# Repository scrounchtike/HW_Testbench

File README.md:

# Template_Hardware
see [KiCad_Library](https://github.com/EclipseETS/KiCad_Library) for detailed instructions

# Structure de projet
| [Nom de votre projet] |                    |        |
|:---:                  | :---:              | :---:  |
|↳                      | Calculs            |        |
|↳                      | DOC                |        |
|↳                      | [Nom du prototype] |        |
|                       |↳                   | [Version du PCB] |

# Utilisation  
1. Demander à un admin de créer un nouveau repo à partir du repo [Template_Hardware](https://github.com/EclipseETS/Template_Hardware).
2. Cloner le nouveau repo sur votre ordinateur.
3. Remplacer les noms des fichiers dans **Project_Template** avec le nom de votre projet **SAUF Project_Template.kicad_wks** .
4. Renommer le dossier **Project_Template** avec la version (Ex.V1,V2 ...) **La hiérarchie de projet doit ressembler à E10/V1/**.
5. Commit et Push les changements au projet. **Les projets HW travaillent directement dans la branche master**

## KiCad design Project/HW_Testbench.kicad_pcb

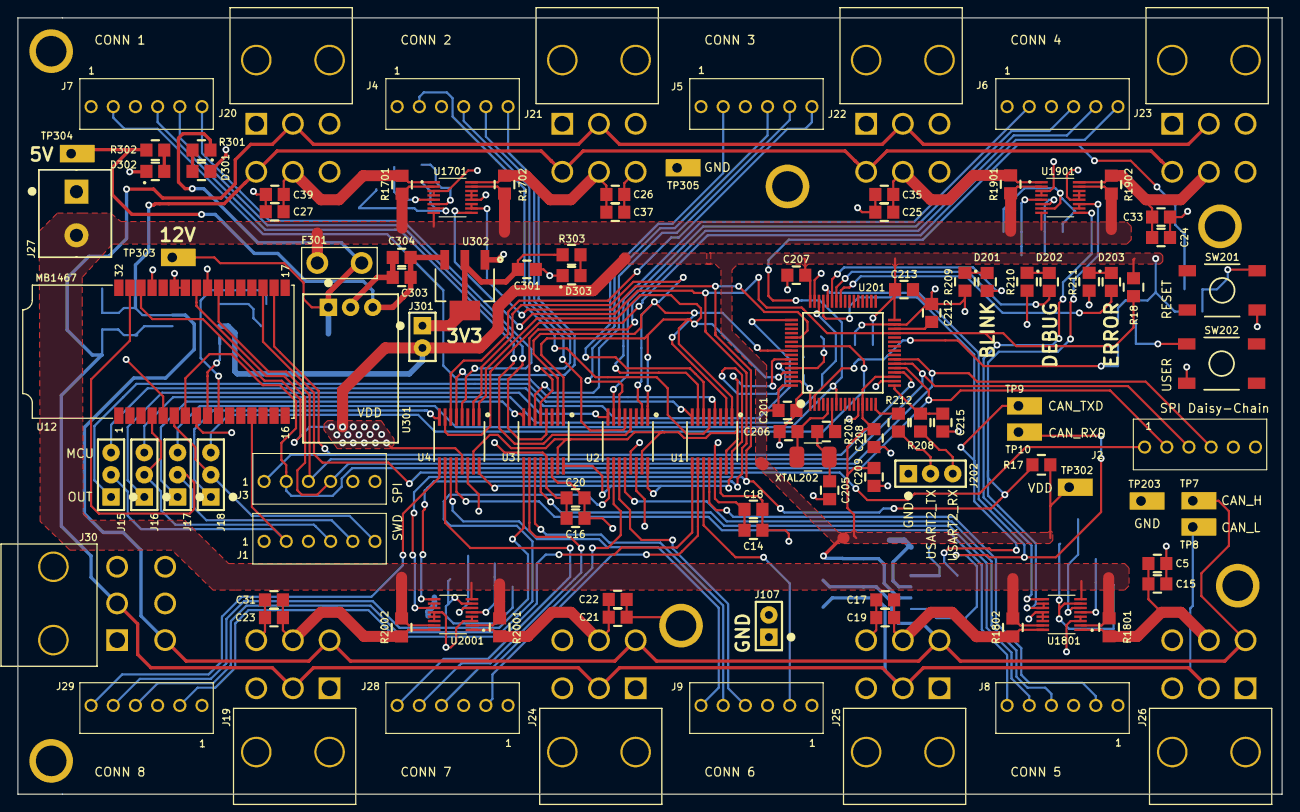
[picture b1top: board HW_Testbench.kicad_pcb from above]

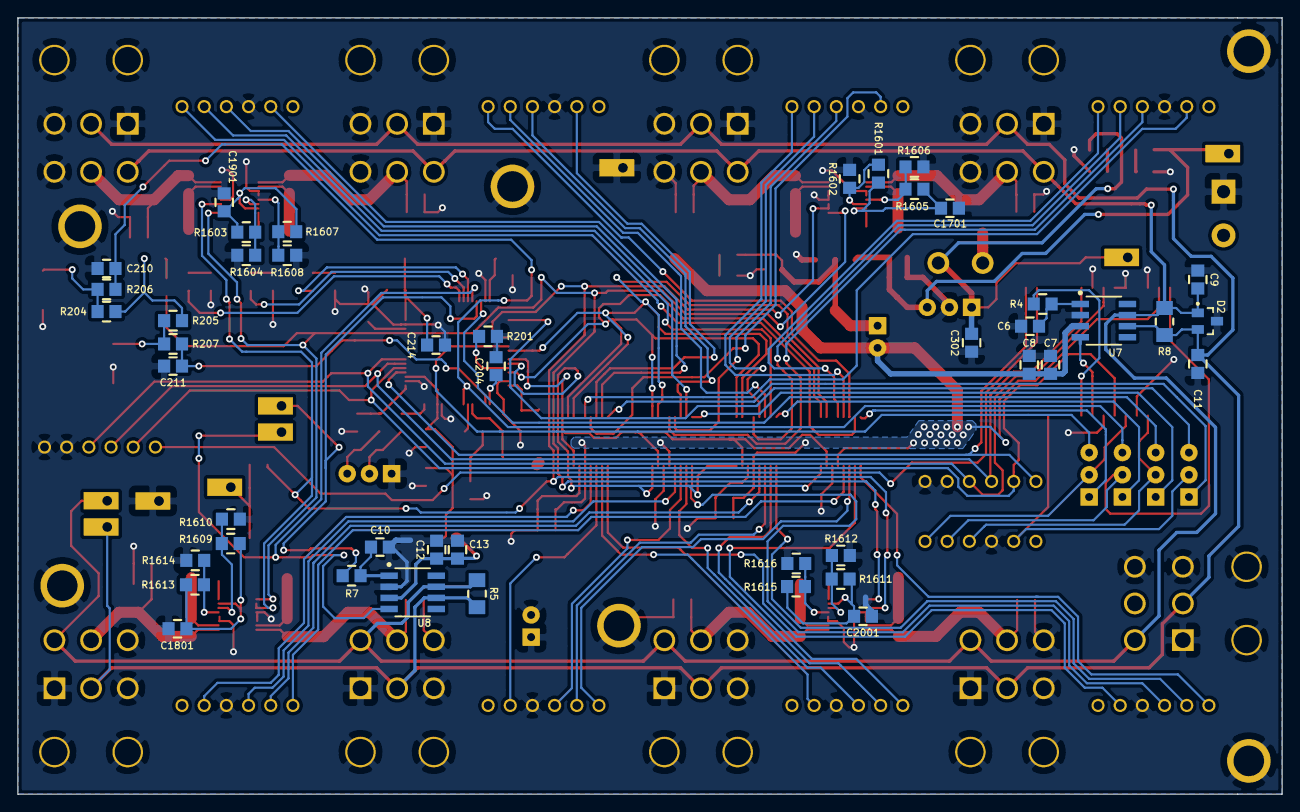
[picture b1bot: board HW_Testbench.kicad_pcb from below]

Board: 2 copper layers, 144.8 x 88.9 mm, 161 parts (45 on the bottom side), 111 nets.

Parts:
C5, C7, C12, C17, C18, C20, C21, C31, C33, C35, C37, C39, C204, C208: 885012107015; C0805
C6, C9, C10, C11: 885012207080; C0805
C8, C13, C14, C15, C16, C19, C22, C23, C24, C25, C26, C27, C201, C207, C210, C211, C213, C214, C1701, C1801, C1901, C2001: 885012207098; C0805
C205, C206, C215: 885012007053; C0805
C209: 885012207092; C0805
C212, C302, C303: 885012107018; C0805
C301: 885012107005; C0805
C304: 885012107014; C0805
D2: D1213A-02SOL-7; SOT-23-3
D201, D301, D302, D303: 150080VS75000; LED_0805_GREEN
D202: 150080YS75000; LED_0805_YELLOW
D203: 150080RS75000; LED_0805_RED
F301: 39511000440; TE5_395
H1, H2, H3, H4, H6, H7: Mounting-Hole-M3; Mounting_Hole_3mm
J1, J2, J3, J4, J5, J6, J7, J8, J9, J28, J29: 61900611121
J15, J16, J17, J18, J202: Header_Male_Pin_2.54mm_1X3_,_Unshrouded; Headers_2.54mm_1X3
J19, J20, J21, J22, J23, J24, J25, J26, J30: 649006227222
J27: 1935161
J107, J301: Header_Male_Pin_2.54mm_1X2_,_Unshrouded; Headers_2.54mm_1X2
R4, R7, R206, R207: RC0805JR-07100RL; R0805
R5, R8: RC1206JR-07120RL; R1206
R17, R18, R204, R205, R208, R301: RC0805JR-074K7L; R0805
R201: RC0805JR-0710KL; R0805
R203, R1601, R1602, R1603, R1604, R1605, R1606, R1607, R1608, R1609, R1610, R1611, R1612, R1613, R1614, R1615, R1616: RC0805JR-070RL; R0805
R209, R210, R211, R303: RC0805JR-07470RL; R0805
R212, R302: RC0805JR-071KL; R0805
R1701, R1702, R1801, R1802, R1901, R1902, R2001, R2002: ERJ-6LWFR005V; R0805
SW201, SW202: PTS645SM43SMTR92; PTS645_6X6X4_SMD
TP7, TP8, TP9, TP10, TP203, TP302, TP303, TP304, TP305: Test_Point_THM; Keystone_5001
U1, U2, U3, U4: TMUX1208PWR; TSSOP-16
U7, U8: SN65HVD232DR; SOIC-8
U12: STLINK-V3MODS; MOD_STLINK-V3M_MB1467
U201: STM32F446RE; LQFP-64
U301: OKI-78SR-5_1.5-W36H-C; OKI-78SR_Horizontal
U302: AZ1117IH-3.3TRG1; SOT-223-3
U1701, U1801, U1901, U2001: LTC2992IMS_PBF; AnalogDevices_16-MSOP
XTAL202: 7A-8.000MAHJ-T; TXC_7A_Series

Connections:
3.3V: C301.2, J301.1, R303.2, U302.2, U302.4
5V: C303.2, C304.2, R302.2, TP304.1, U301.3, U302.3
12V: C302.2, F301.2, R301.2, TP303.1, U301.1
/ADR_0: U1.1, U2.1, U3.1, U4.1, U201.61
/ADR_1: U1.16, U2.16, U3.16, U4.16, U201.59
/ADR_2: U1.15, U2.15, U3.15, U4.15, U201.58
/CAN1_RXD: TP10.1, U8.4, U201.44
/CAN1_TXD: R7.1, TP9.1, U201.45
/CAN_Connectors/12V_Conn1: C27.1, C39.2, J20.5, R1701.1, U1701.1
/CAN_Connectors/12V_Conn2: C26.1, C37.2, J21.5, R1702.2, U1701.16
/CAN_Connectors/12V_Conn3: C25.1, C35.2, J22.5, R1901.1, U1901.1
/CAN_Connectors/12V_Conn4: C24.1, C33.2, J23.5, R1902.2, U1901.16
/CAN_Connectors/12V_Conn5: C5.2, C15.1, J26.5, R1801.1, U1801.1
/CAN_Connectors/12V_Conn6: C17.2, C19.1, J25.5, R1802.2, U1801.16
/CAN_Connectors/12V_Conn7: C21.2, C22.1, J24.5, R2001.1, U2001.1
/CAN_Connectors/12V_Conn8: C23.1, C31.2, J19.5, R2002.2, U2001.16
/CAN_Connectors/CAN_H: C9.1, D2.1, J19.4, J20.4, J21.4, J22.4, J23.4, J24.4, J25.4, J26.4, J30.4, R5.1, R8.1, TP7.1, U7.7, U8.7
/CAN_Connectors/CAN_L: C11.1, D2.2, J19.2, J20.2, J21.2, J22.2, J23.2, J24.2, J25.2, J26.2, J30.2, R5.2, R8.2, TP8.1, U7.6, U8.6
/CAN_Connectors/CurrentSense/sheet60485D35/I2C_ADR0: R1601.2, R1602.1, U1701.6
/CAN_Connectors/CurrentSense/sheet60485D35/I2C_ADR1: R1605.2, R1606.1, U1701.5
/CAN_Connectors/CurrentSense/sheet60485D35/INTVcc: C1701.1, R1601.1, R1605.1, U1701.7
/CAN_Connectors/CurrentSense/sheet60485D36/I2C_ADR0: R1609.2, R1610.1, U1801.6
/CAN_Connectors/CurrentSense/sheet60485D36/I2C_ADR1: R1613.2, R1614.1, U1801.5
/CAN_Connectors/CurrentSense/sheet60485D36/INTVcc: C1801.1, R1609.1, R1613.1, U1801.7
/CAN_Connectors/CurrentSense/sheet60485D37/I2C_ADR0: R1603.2, R1604.1, U1901.6
/CAN_Connectors/CurrentSense/sheet60485D37/I2C_ADR1: R1607.2, R1608.1, U1901.5
/CAN_Connectors/CurrentSense/sheet60485D37/INTVcc: C1901.1, R1603.1, R1607.1, U1901.7
/CAN_Connectors/CurrentSense/sheet60485D38/I2C_ADR0: R1611.2, R1612.1, U2001.6
/CAN_Connectors/CurrentSense/sheet60485D38/I2C_ADR1: R1615.2, R1616.1, U2001.5
/CAN_Connectors/CurrentSense/sheet60485D38/INTVcc: C2001.1, R1611.1, R1615.1, U2001.7
/CONN_NRST: J1.5, J17.2, U12.31
/CONN_SWCLK: J1.2, J15.2, U12.13
/CONN_SWDIO: J1.4, J16.2, U12.4
/CONN_SWO: J1.6, J18.2, U12.6
/CS_SCL: R18.2, U201.29, U1701.9, U1801.9, U1901.9, U2001.9
/CS_SDA: R17.2, U201.53, U1701.10, U1701.11, U1801.10, U1801.11, U1901.10, U1901.11, U2001.10, U2001.11
/DAISYCHAIN_SPI_NSS: J2.1, U12.19
/MCU_NRST: C210.1, J17.3, R206.2, U201.7
/MCU_SWCLK: J15.3, U201.49
/MCU_SWDIO: J16.3, U201.46
/MCU_SWO: J18.3, U201.55
/OUT_NRST: J17.1, U3.8
/OUT_SWCLK: J15.1, U1.8
/OUT_SWDIO: J16.1, U2.8
/OUT_SWO: J18.1, U4.8
/PA4: J3.1, U12.18, U201.20
/PA5: J2.2, J3.2, U12.7, U201.21
/PA6: J2.3, J3.3, U12.23, U201.22
/PA7: J2.4, J3.4, U12.25, U201.23
/PB4: U1.2, U2.2, U3.2, U4.2, U201.56
/STLINK_CAN_RXD: U7.4, U12.9
/STLINK_CAN_TXD: R4.1, U12.10
/STM32F446/BLINK: D201.2, U201.43
/STM32F446/DEBUG: D202.2, U201.42
/STM32F446/ERROR: D203.2, U201.41
/STM32F446/HSE_IN: C206.1, U201.5, XTAL202.2
/STM32F446/HSE_OUT: R203.1, U201.6
/STM32F446/PA2: R212.2, U201.16
/STM32F446/PA3: C215.2, R208.2, U201.17
/STM32F446/USART2_RX: J202.3, R208.1
/STM32F446/USART2_TX: J202.2, R212.1
/STM32F446/USER_BTN: C211.1, R207.2, U201.2
/SWD_Connecteurs/NRST_1: J7.5, U3.4
/SWD_Connecteurs/NRST_2: J4.5, U3.5
/SWD_Connecteurs/NRST_3: J5.5, U3.6
/SWD_Connecteurs/NRST_4: J6.5, U3.7
/SWD_Connecteurs/NRST_5: J8.5, U3.12
/SWD_Connecteurs/NRST_6: J9.5, U3.11
/SWD_Connecteurs/NRST_7: J28.5, U3.10
/SWD_Connecteurs/NRST_8: J29.5, U3.9
/SWD_Connecteurs/SWCLK_1: J7.2, U1.4
/SWD_Connecteurs/SWCLK_2: J4.2, U1.5
/SWD_Connecteurs/SWCLK_3: J5.2, U1.6
/SWD_Connecteurs/SWCLK_4: J6.2, U1.7
/SWD_Connecteurs/SWCLK_5: J8.2, U1.12
/SWD_Connecteurs/SWCLK_6: J9.2, U1.11
/SWD_Connecteurs/SWCLK_7: J28.2, U1.10
/SWD_Connecteurs/SWCLK_8: J29.2, U1.9
/SWD_Connecteurs/SWDIO_1: J7.4, U2.4
/SWD_Connecteurs/SWDIO_2: J4.4, U2.5
/SWD_Connecteurs/SWDIO_3: J5.4, U2.6
/SWD_Connecteurs/SWDIO_4: J6.4, U2.7
/SWD_Connecteurs/SWDIO_5: J8.4, U2.12
/SWD_Connecteurs/SWDIO_6: J9.4, U2.11
/SWD_Connecteurs/SWDIO_7: J28.4, U2.10
/SWD_Connecteurs/SWDIO_8: J29.4, U2.9
/SWD_Connecteurs/SWO_1: J7.6, U4.4
/SWD_Connecteurs/SWO_2: J4.6, U4.5
/SWD_Connecteurs/SWO_3: J5.6, U4.6
/SWD_Connecteurs/SWO_4: J6.6, U4.7
/SWD_Connecteurs/SWO_5: J8.6, U4.12
/SWD_Connecteurs/SWO_6: J9.6, U4.11
/SWD_Connecteurs/SWO_7: J28.6, U4.10
/SWD_Connecteurs/SWO_8: J29.6, U4.9
/VBat: C204.2, U201.1
CAN_PWR: F301.1, J27.2, R1701.2, R1702.1, R1801.2, R1802.1, R1901.2, R1902.1, R2001.2, R2002.1, U1701.2, U1701.8, U1701.15, U1801.2, U1801.8, U1801.15, U1901.2, U1901.8, U1901.15, U2001.2, U2001.8, U2001.15
DGND: C5.1, C6.2, C7.1, C8.1, C9.2, C10.2, C11.2, C12.1, C13.1, C14.1, C15.2, C16.1, C17.1, C18.2, C19.2, C20.2, C21.1, C22.2, C23.2, C24.2, C25.2, C26.2, C27.2, C31.1, C33.1, C35.1, C37.1, C39.1, C201.1, C204.1, C205.1, C206.2, C207.2, C208.1, C209.1, C210.2, C211.2, C212.1, C213.2, C214.2, C215.1, C301.1, C302.1, C303.1, C304.1, C1701.2, C1801.2, C1901.2, C2001.2, D2.3, D301.1, D302.1, D303.1, H1.1, H2.1, H3.1, H4.1, H6.1, H7.1, J1.3, J2.5, J2.6, J3.5, J3.6, J4.3, J5.3, J6.3, J7.3, J8.3, J9.3, J19.1, J19.3, J19.6, J19.7, J19.8, J20.1, J20.3, J20.6, J20.7, J20.8, J21.1, J21.3, J21.6, J21.7, J21.8, J22.1, J22.3, J22.6, J22.7, J22.8, J23.1, J23.3, J23.6, J23.7, J23.8, J24.1, J24.3, J24.6, J24.7, J24.8, J25.1, J25.3, J25.6, J25.7, J25.8, J26.1, J26.3, J26.6, J26.7, J26.8, J27.1, J28.3, J29.3, J30.1, J30.3, J30.6, J30.7, J30.8, J107.1, J107.2, J202.1, R201.1, R209.1, R210.1, R211.1, R1602.2, R1604.2, R1606.2, R1608.2, R1610.2, R1612.2, R1614.2, R1616.2, SW201.4, SW202.3, TP203.1, TP305.1, U1.14, U2.14, U3.14, U4.14, U7.2, U8.2, U12.5, U12.8, U12.24, U12.26, U12.27, U12.29, U201.12, U201.18, U201.31, U201.47, U201.63, U301.2, U302.1, U1701.3, U1701.4, U1701.12, U1701.13, U1701.14, U1801.3, U1801.4, U1801.12, U1801.13, U1801.14, U1901.3, U1901.4, U1901.12, U1901.13, U1901.14, U2001.3, U2001.4, U2001.12, U2001.13, U2001.14
unnamed: C6.1, R4.2, U7.1
unnamed: C10.1, R7.2, U8.1
unnamed: C205.2, R203.2, XTAL202.1
unnamed: C212.2, U201.30
unnamed: D201.1, R209.2
unnamed: D202.1, R210.2
unnamed: D203.1, R211.2
unnamed: D301.2, R301.1
unnamed: D302.2, R302.1
unnamed: D303.2, R303.1
unnamed: R201.2, U201.60
unnamed: R204.1, R206.1, SW201.2
unnamed: R205.1, R207.1, SW202.1
VDD: C7.2, C8.2, C12.2, C13.2, C14.2, C16.2, C18.1, C20.1, C201.2, C207.1, C208.2, C209.2, C213.1, C214.1, J301.2, R17.1, R18.1, R204.2, R205.2, TP302.1, U1.13, U2.13, U3.13, U4.13, U7.3, U8.3, U12.30, U201.13, U201.19, U201.32, U201.48, U201.64

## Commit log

2021-01-09 HW Testbench board
2021-01-16 last changes
2021-03-07 Code review changes
